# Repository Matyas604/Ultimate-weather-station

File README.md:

# Ultimate weather station
For a long time, I’ve wanted to know the current temperature, humidity, air quality, and more outside. Since weather forecasts are never accurate for my exact location, I wanted to know what the conditions really are. So, since I already have a lot of experience, I decided to build a complete weather station that would measure the values I wanted, based exactly on the sensors I chose. And since I have a [Home Assistant](https://www.home-assistant.io/) at home, I could make the station smart and monitor the data from anywhere.

This project was more about 3D modeling than PCB design, but in the end, I’m very satisfied.

## Features
- **Contains sensors:** [SHT45](https://sensirion.com/media/documents/33FD6951/67EB9032/HT_DS_Datasheet_SHT4x_5.pdf), [BMP280](https://www.bosch-sensortec.com/media/boschsensortec/downloads/datasheets/bst-bmp280-ds001.pdf), [SGP41](https://sensirion.com/media/documents/5FE8673C/61E96F50/Sensirion_Gas_Sensors_Datasheet_SGP41.pdf), and the [AS3935](https://cdn.sparkfun.com/assets/learn_tutorials/9/2/1/AS3935_Datasheet_EN_v2.pdf) and [LM393](https://www.onsemi.com/download/data-sheet/pdf/lm393-d.pdf) integrated circuits  
- **It can measure:** [temperature](https://en.wikipedia.org/wiki/Temperature), [humidity](https://en.wikipedia.org/wiki/Humidity), [pressure](https://en.wikipedia.org/wiki/Atmospheric_pressure), [air quality](https://en.wikipedia.org/wiki/Air_quality_index), [lightning distance and energy](https://en.wikipedia.org/wiki/Lightning), [wind speed](https://en.wikipedia.org/wiki/Wind_speed) and whether it is raining
- It's connected to [Home Assistant](https://www.home-assistant.io/), so I can use the data to set up automations and monitor the readings even when I'm not at home
- The [ESP32-S3](https://documentation.espressif.com/esp32-s3_datasheet_en.pdf) is the brain of the entire station
- It has two PCBs, one main board and another with sensors located inside the [radiation shield](https://en.wikipedia.org/wiki/Stevenson_screen) that measure the readings. They are connected to each other with a 7-wire cable
- It has pull-up resistors for I2C on the main board, additional resistors can be added on the sensor board to extend the cable length beyond 2 meters
- It is programmable via USB-C
- It is powered by a 5V two-wire cable

⚠️The screw and nuts for the anemometer and the rods for the radiation shield must be made of brass, because brass is non-magnetic and therefore will not interfere with the lightning detection antenna, unlike iron or steel!

## CAD model
It includes a box for the main board and a radiation shield, which is secured with M5 rods and nuts, on top is an anemometer propeller for measuring wind speed. I’ll be placing the weather station on the balcony, so I’ve made a mount for it. It will be attached to the railing, which has a 14° slope, so the mount is designed to keep the radiation shield straight. The shield is connected to the mount with an M6 rod and M6 nuts, there is also a mount for the rain sensor. The railing mount is secured with two parts connected by M6 bolts and nuts. **All parts must be printed using at least ABS, but ASA would be much better, they must also be white!** They will be kept outdoors permanently, and ASA is a material that is highly resistant to UV radiation, sunlight, and rain. It is also very strong, so it can withstand strong winds.

<p align="center">
  <strong>Made in Fusion360</strong>
</p>

## PCBs
### Main PCB:
<p align="center">
  Schematic
</p>

<p align="center">
  PCB
</p>

### Sensors PCB:
<p align="center">
  Schematic
</p>

<p align="center">
  PCB
</p>

<p align="center">
  <strong>Made in KiCad</strong>
</p>

## Wiring diagram

## Firmware
This weather station uses [ESPHome](https://esphome.io/) firmware. It is programmed via the USB-C port on the main board. Thanks to ESPHome, it connects to [Home Assistant](https://www.home-assistant.io/), where I can then create various automations and view data from anywhere.

## BOM
It's very long, so you can find it in .csv format [here](https://github.com/Matyas604/Ultimate-weather-station/blob/main/BOM.csv).  
Please read additional information about the BOM [here](https://github.com/Matyas604/Ultimate-weather-station/blob/main/BOM%20info.md).

## Notes for v2 upgrades
Since I anticipated potential upgrades, I added additional I2C ports to both the main board and the sensor board. On the main board, you can also select a voltage of 5V or 3.3V, so you can connect a lot of other things. I did this so I wouldn’t have to replace the entire board when adding expansions. The main board also features a very powerful ESP32, which has enough performance for further expansion. I plan to add the following over time:
- A rain gauge that measures the amount of rainfall
- A dust sensor for measuring **PM1.0**, **PM2.5**, **PM4**, and **PM10** particles, which can then be used in combination with the **SGP41** to calculate air [**Quality Index (AQI)**](https://en.wikipedia.org/wiki/Air_quality_index) values
- Wind direction
- UV and light sensor

## License
This project is licensed under the GNU GPL v3.
```
Matyas604/Ultimate-weather-station - Custom weather station for Home Assistant running on an ESP32
Copyright (C) 2026 Matyáš Caha

This program is free software: you can redistribute it and/or modify
it under the terms of the GNU General Public License as published by
the Free Software Foundation, either version 3 of the License, or
(at your option) any later version.

This program is distributed in the hope that it will be useful,
but WITHOUT ANY WARRANTY; without even the implied warranty of
MERCHANTABILITY or FITNESS FOR A PARTICULAR PURPOSE. See the
GNU General Public License for more details.

You should have received a copy of the GNU General Public License
along with this program. If not, see <https://www.gnu.org/licenses/>.
```

<hr>

<p align="center">
  Made with ❤️ by <a href="https://github.com/Matyas604">@Matyas604</a>
</p>

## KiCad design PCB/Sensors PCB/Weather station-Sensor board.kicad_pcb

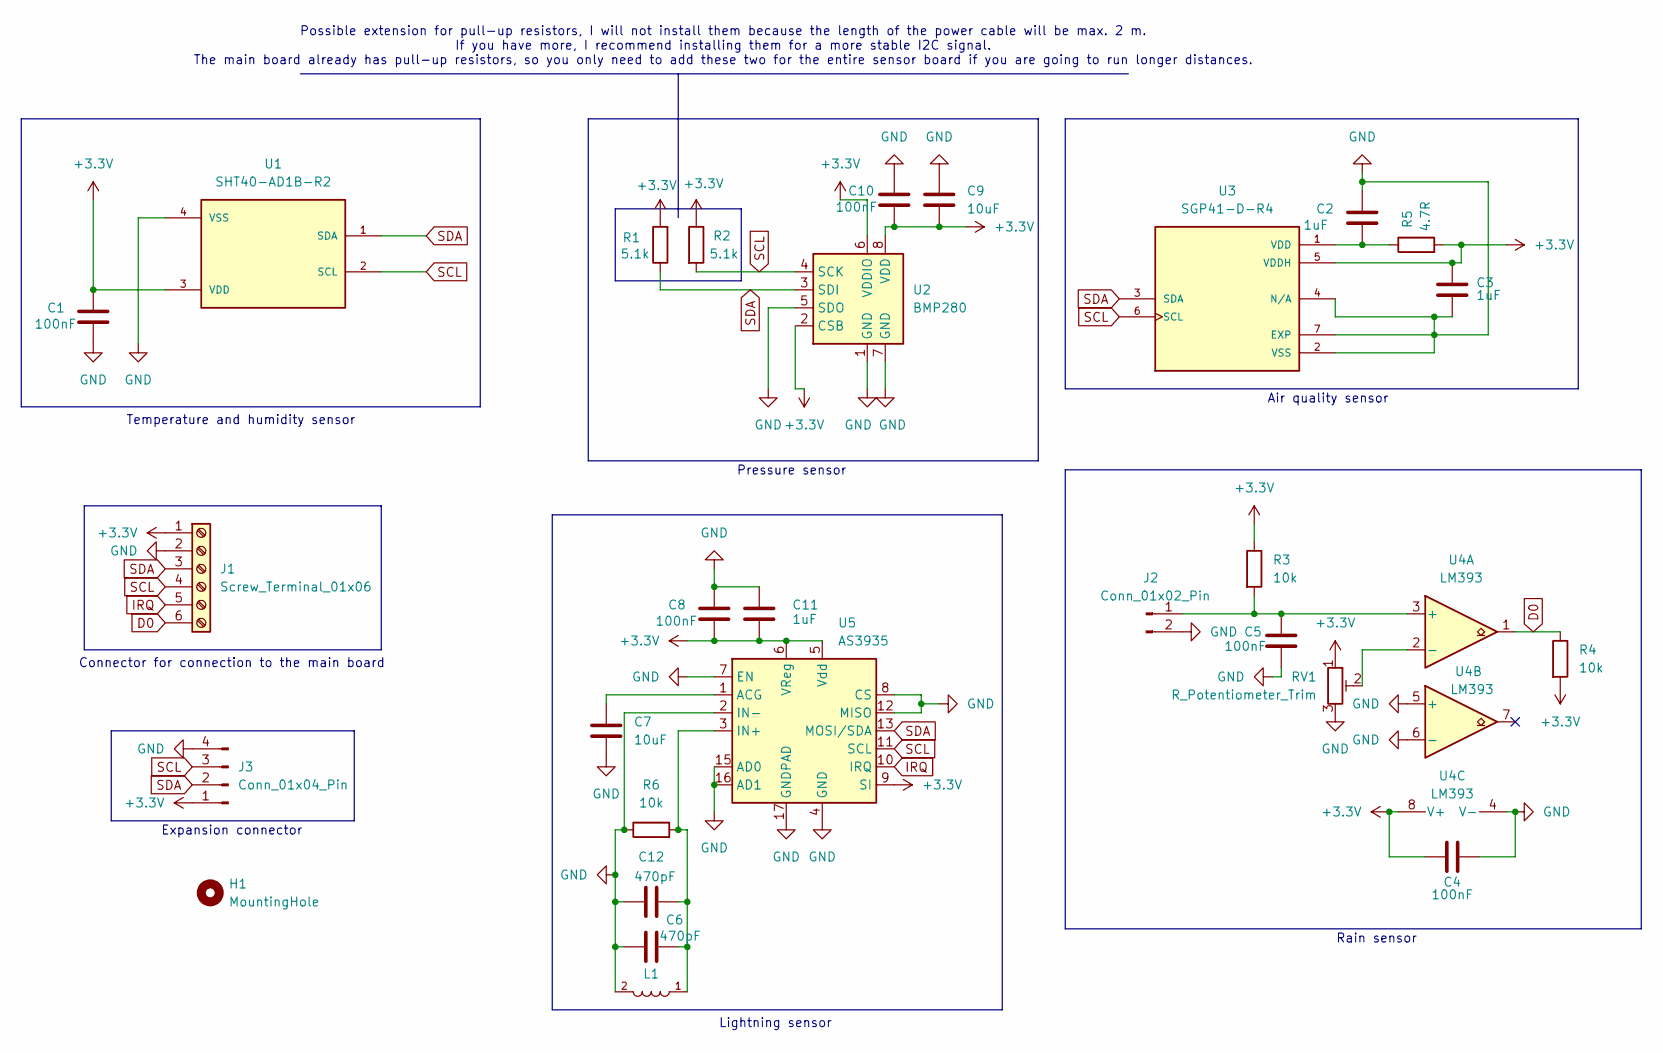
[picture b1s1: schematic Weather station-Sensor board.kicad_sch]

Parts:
C1, C4, C5, C8, C10: 100nF; C_0805_2012Metric
C2, C3, C11: 1uF; C_0805_2012Metric
C6, C12: 470pF; C_0805_2012Metric
C7, C9: 10uF; C_0805_2012Metric
H1: MountingHole; MountingHole_3.2mm_M3
J1: Screw_Terminal_01x06; TerminalBlock_Phoenix_MKDS-1,5-6-5.08_1x06_P5.08mm_Horizont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
J2: Conn_01x02_Pin; PinHeader_1x02_P2.54mm_Vertical
J3: Conn_01x04_Pin; PinHeader_1x04_P2.54mm_Vertical
L1: 100uH; MA5532-AE
R1, R2: 5.1k; R_0805_2012Metric
R3, R4, R6: 10k; R_0805_2012Metric
R5: 4.7R; R_0805_2012Metric
RV1: R_Potentiometer_Trim; Potentiometer_Bourns_3314G_Vertical
U1: SHT40-AD1B-R2; SHT4X
U2: BMP280; Bosch_LGA-8_2x2.5mm_P0.65mm_ClockwisePinNumbering
U3: SGP41-D-R4; XDCR_SGP41-D-R4; PARTREV 1.0
U4: LM393; SOIC-8_3.9x4.9mm_P1.27mm
U5: AS3935; MLPQ-16-1EP_4x4mm_P0.65mm_EP2.8x2.8mm

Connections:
+3.3V: C1.1, C3.1, C4.2, C8.2, C9.2, C10.2, C11.2, J1.1, J3.1, R1.2, R2.1, R3.1, R4.2, R5.2, RV1.1, U1.3 (VDD), U2.2 (CSB), U2.6 (VDDIO), U2.8 (VDD), U3.5 (VDDH), U4.8 (V+), U5.5 (Vdd), U5.6 (VReg), U5.9 (SI)
D0: J1.6, R4.1, U4.1
GND: C1.2, C2.1, C3.2, C4.1, C5.2, C6.1, C7.2, C8.1, C9.1, C10.1, C11.1, C12.1, J1.2, J2.2, J3.4, L1.2, R6.1, RV1.3, U1.4 (VSS), U2.1 (GND), U2.5 (SDO), U2.7 (GND), U3.2 (VSS), U3.4 (N/A), U3.7 (EXP), U4.4 (V-), U4.5 (+), U4.6 (-), U5.2 (IN-), U5.4 (GND), U5.7 (EN), U5.8 (CS), U5.12 (MISO), U5.15 (AD0), U5.16 (AD1), U5.17 (GNDPAD)
IRQ: J1.5, U5.10 (IRQ)
unnamed: C5.1, J2.1, R3.2, U4.3 (+)
unnamed: C2.2, R5.1, U3.1 (VDD)
unnamed: RV1.2, U4.2 (-)
unnamed: C7.1, U5.1 (ACG)
unnamed: C6.2, C12.2, L1.1, R6.2, U5.3 (IN+)
SCL: J1.4, J3.3, R2.2, U1.2 (SCL), U2.4 (SCK), U3.6 (SCL), U5.11 (SCL)
SDA: J1.3, J3.2, R1.1, U1.1 (SDA), U2.3 (SDI), U3.3 (SDA), U5.13 (MOSI/SDA)

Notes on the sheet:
Lightning sensor
Rain sensor
Expansion connector
Pressure sensor
Connector for connection to the main board
Possible extension for pull-up resistors, I will not install them because the length of the power cable will be max. 2 m. If you have more, I recommend installing them for a more stable I2C signal. The main board already has pull-up resistors, so you only need to add these two for the entire sensor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
Temperature and humidity sensor
Air quality sensor

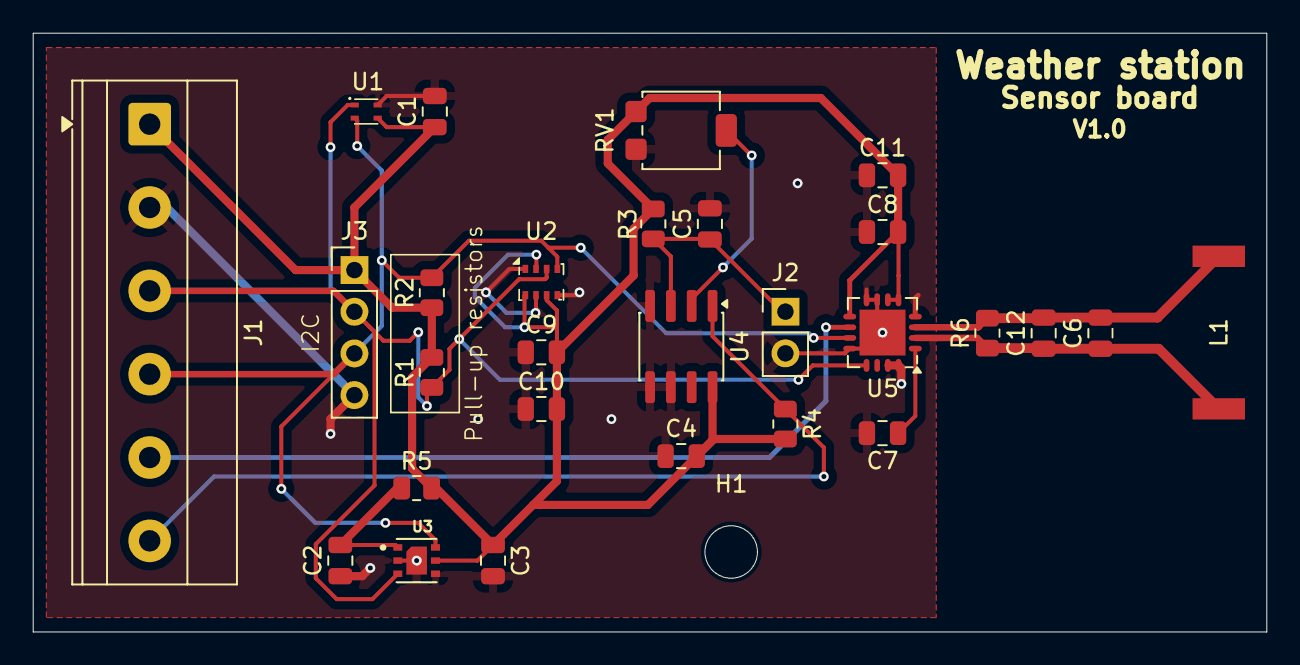
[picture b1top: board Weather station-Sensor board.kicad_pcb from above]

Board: 2 copper layers, 75.2 x 36.5 mm, 29 parts (0 on the bottom side), 11 nets.

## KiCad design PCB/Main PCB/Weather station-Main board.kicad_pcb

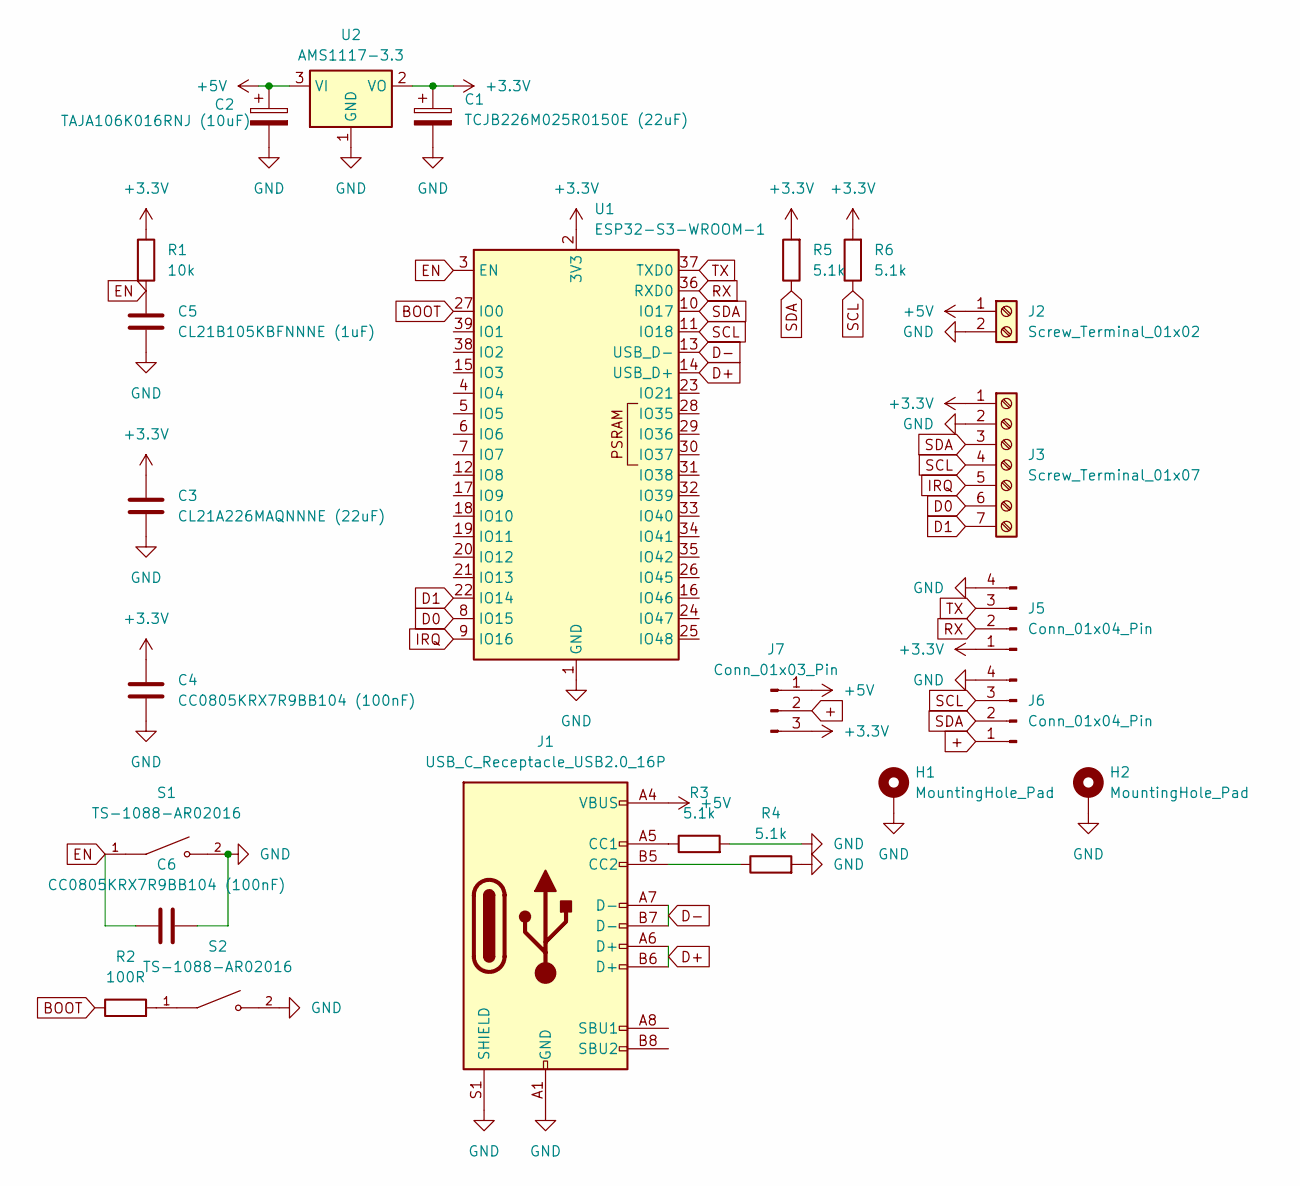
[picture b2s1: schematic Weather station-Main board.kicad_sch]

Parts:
C1: TCJB226M025R0150E (22uF); CP_EIA-3528-21_Kemet-B
C2: TAJA106K016RNJ (10uF); CP_EIA-3216-18_Kemet-A
C3: CL21A226MAQNNNE (22uF); C_0805_2012Metric
C4, C6: CC0805KRX7R9BB104 (100nF); C_0805_2012Metric
C5: CL21B105KBFNNNE (1uF); C_0805_2012Metric
H1, H2: MountingHole_Pad; MountingHole_3.2mm_M3_Pad_Via
J1: USB_C_Receptacle_USB2.0_16P; USB_C_Receptacle_HRO_TYPE-C-31-M-12
J2: Screw_Terminal_01x02; TerminalBlock_Phoenix_MKDS-1,5-2-5.08_1x02_P5.08mm_Horizont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
J3: Screw_Terminal_01x07; TerminalBlock_Phoenix_MKDS-1,5-7-5.08_1x07_P5.08mm_Horizont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
J5, J6: Conn_01x04_Pin; PinHeader_1x04_P2.54mm_Vertical
J7: Conn_01x03_Pin; PinHeader_1x03_P2.54mm_Vertical
R1: 10k; R_0805_2012Metric
R2: 100R; R_0805_2012Metric
R3, R4, R5, R6: 5.1k; R_0805_2012Metric
S1, S2: TS-1088-AR02016; SW_TS-1088-AR02016; PARTREV N/A
U1: ESP32-S3-WROOM-1
U2: AMS1117-3.3; SOT-223-3_TabPin2

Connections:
+: J6.1, J7.2
+3.3V: C1.1, C3.1, C4.1, J3.1, J5.1, J7.3, R1.1, R5.2, R6.2, U1.2 (3V3), U2.2 (VO)
+5V: C2.1, J1.A4 (VBUS), J1.A9 (VBUS), J1.B4 (VBUS), J1.B9 (VBUS), J2.1, J7.1, U2.3 (VI)
BOOT: R2.1, U1.27 (IO0)
D0: J3.6, U1.8 (IO15)
D1: J3.7, U1.22 (IO14)
D+: J1.A6 (D+), J1.B6 (D+), U1.14 (USB_D+)
D-: J1.A7 (D-), J1.B7 (D-), U1.13 (USB_D-)
EN: C5.2, C6.1, R1.2, S1.1, U1.3 (EN)
GND: C1.2, C2.2, C3.2, C4.2, C5.1, C6.2, H1.1, H2.1, J1.A1 (GND), J1.A12 (GND), J1.B1 (GND), J1.B12 (GND), J1.S1 (SHIELD), J2.2, J3.2, J5.4, J6.4, R3.2, R4.2, S1.2, S2.2, U1.1 (GND), U1.40 (GND), U1.41 (GND), U2.1 (GND)
IRQ: J3.5, U1.9 (IO16)
unnamed: J1.A5 (CC1), R3.1
unnamed: J1.B5 (CC2), R4.1
unnamed: R2.2, S2.1
RX: J5.2, U1.36 (RXD0)
SCL: J3.4, J6.3, R6.1, U1.11 (IO18)
SDA: J3.3, J6.2, R5.1, U1.10 (IO17)
TX: J5.3, U1.37 (TXD0)

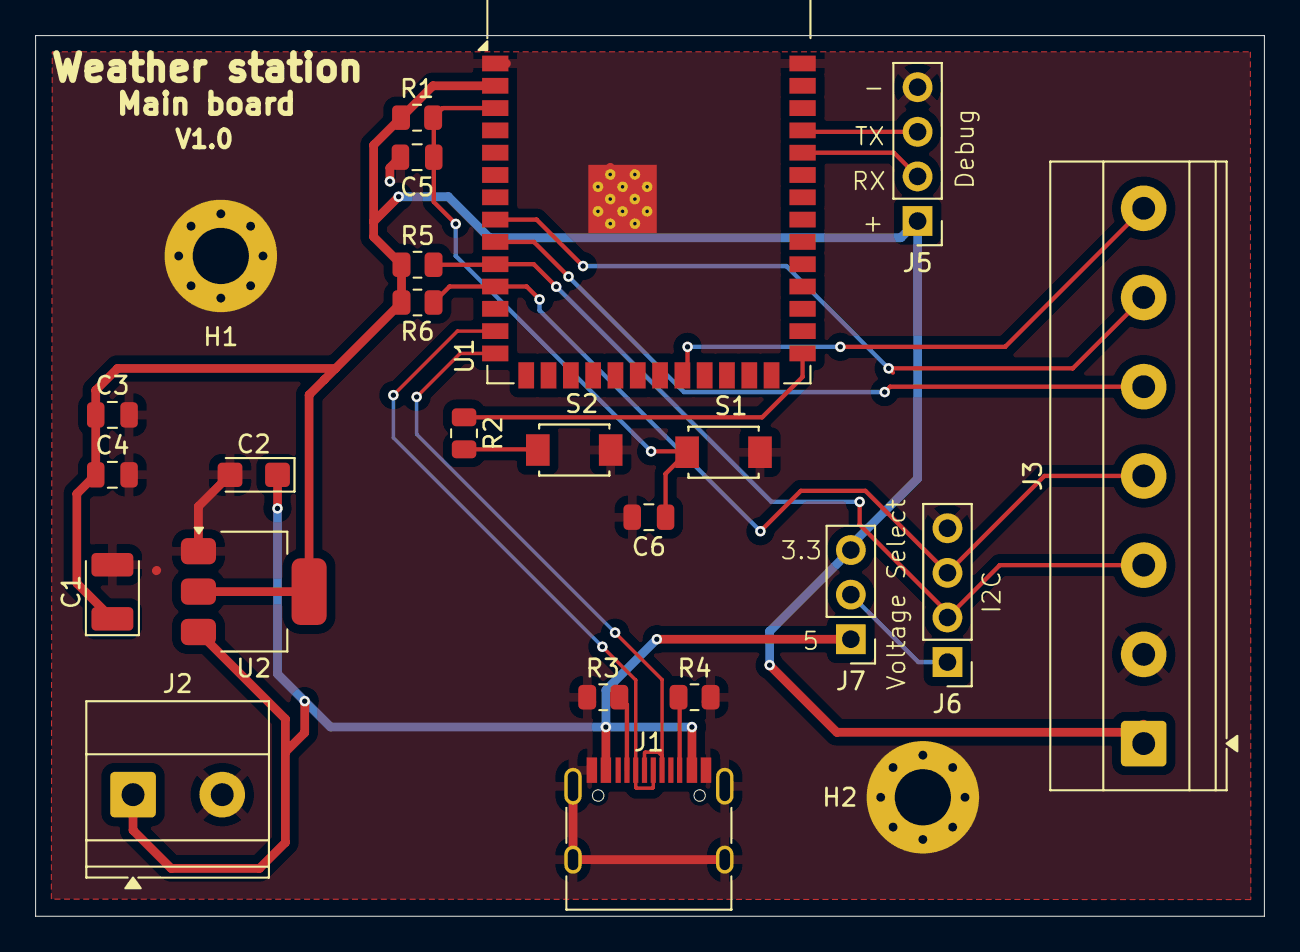
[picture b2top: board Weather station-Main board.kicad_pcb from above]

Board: 2 copper layers, 70.0 x 50.1 mm, 24 parts (0 on the bottom side), 18 nets.

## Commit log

2026-03-08 Adding files
2026-03-23 Adding firmware
2026-03-23 Adding PCB files
2026-03-23 Bad firmware
2026-03-24 Create BOM
2026-03-24 Main PCB components added
2026-03-28 Adding sensors PCB parts and assembly parts
2026-03-28 Adding photos
2026-03-28 Adding few tings
2026-03-28 Adding cart photos
2026-03-29 Adding 3D parts
2026-03-29 Adding LCSC cart photos
2026-03-29 Amount change
2026-03-30 Adding Wiring diagram
2026-03-30 Fix f3z to f3d
2026-04-09 Adding nut caps
2026-04-09 Price changes
2026-04-14 Create LICENSE
